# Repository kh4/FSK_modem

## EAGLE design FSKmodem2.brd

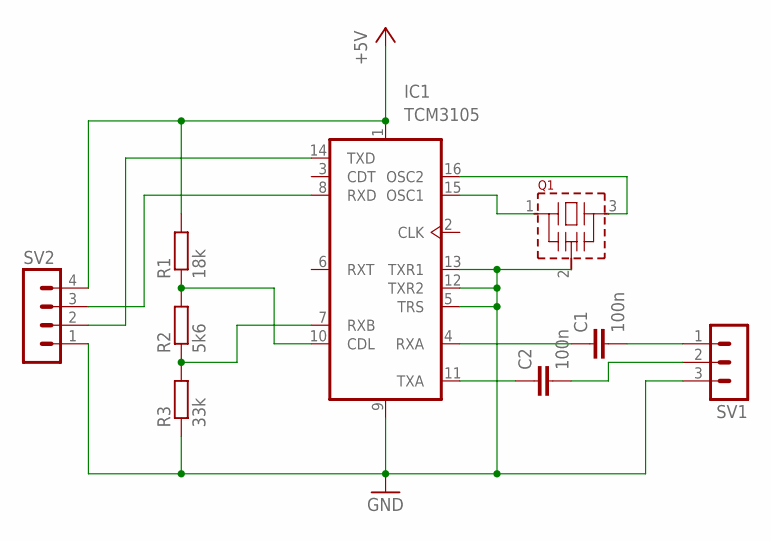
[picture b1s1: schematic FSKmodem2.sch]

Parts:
C1, C2: 100n; C050-024X044
IC1: TCM3105; DIL16
Q1: CSTLS_G; CSTLS_G8
R1: 18k; 0204/5
R2: 5k6; 0204/5
R3: 33k; 0204/5
SV1: MA03-1
SV2: MA04-1

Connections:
+5V: IC1.1 (VDD), R1.2, SV2.4
GND: IC1.5 (TRS), IC1.9 (VSS), IC1.12 (TXR2), IC1.13 (TXR1), Q1.2 (VSS), R3.1, SV1.3, SV2.1
unnamed: IC1.10 (CDL), R1.1, R2.2
unnamed: IC1.15 (OSC1), Q1.1
unnamed: C2.2, SV1.2
unnamed: C1.1, IC1.4 (RXA)
unnamed: C2.1, IC1.11 (TXA)
unnamed: C1.2, SV1.1
unnamed: IC1.7 (RXB), R2.1, R3.2
unnamed: IC1.14 (TXD), SV2.2
unnamed: IC1.8 (RXD), SV2.3
unnamed: IC1.16 (OSC2), Q1.3

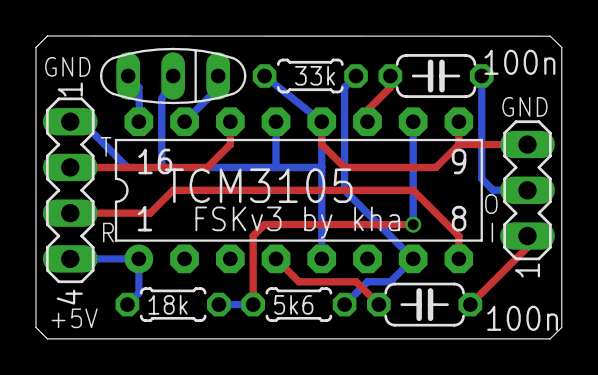
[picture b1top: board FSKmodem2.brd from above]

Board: 2 copper layers, 29.2 x 16.8 mm, 9 parts (0 on the bottom side), 12 nets.

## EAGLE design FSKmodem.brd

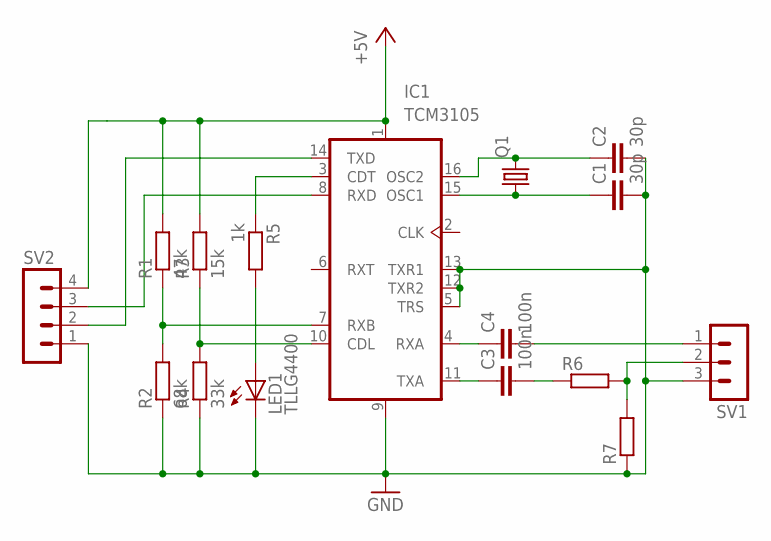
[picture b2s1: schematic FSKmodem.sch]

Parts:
C1, C2: 30p; C025-024X044
C3, C4: 100n; C025-024X044
IC1: TCM3105; DIL16
LED1: TLLG4400; LED3MM
Q1: CRYSTALHC49U70; HC49U70
R1: 47k; 0204/5
R2: 68k; 0204/5
R3: 15k; 0204/5
R4: 33k; 0204/5
R5: 1k; 0204/5
R6, R7: R-EU_0204/5; 0204/5
SV1: MA03-1
SV2: MA04-1

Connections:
+5V: IC1.1 (VDD), R1.2, R3.2, SV2.4
GND: C1.2, C2.2, IC1.5 (TRS), IC1.9 (VSS), IC1.12 (TXR2), IC1.13 (TXR1), LED1.K (C), R2.1, R4.1, R7.1, SV1.3, SV2.1
unnamed: C2.1, IC1.16 (OSC2), Q1.2
unnamed: C1.1, IC1.15 (OSC1), Q1.1
unnamed: C3.2, R6.1
unnamed: C4.1, IC1.4 (RXA)
unnamed: C3.1, IC1.11 (TXA)
unnamed: C4.2, SV1.1
unnamed: LED1.A, R5.2
unnamed: IC1.14 (TXD), SV2.2
unnamed: IC1.8 (RXD), SV2.3
unnamed: IC1.10 (CDL), R3.1, R4.2
unnamed: IC1.7 (RXB), R1.1, R2.2
unnamed: IC1.3 (CDT), R5.1
unnamed: R6.2, R7.2, SV1.2

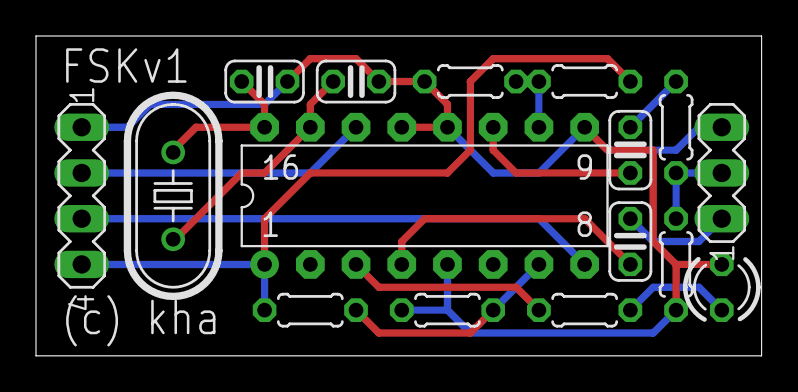
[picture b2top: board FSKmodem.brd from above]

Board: 2 copper layers, 40.3 x 17.8 mm, 16 parts (0 on the bottom side), 15 nets.

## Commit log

2012-07-07 v2 with less parts
2012-07-07 Fixing the resistors, they were so wrong
2012-07-07 final v2
2015-10-12 Change to 5mm long resistors
    This also makes boards smaller ~ 30x17mm
2015-10-12 round corners a bit
